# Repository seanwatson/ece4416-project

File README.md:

Engineering 4th Year Design Project:
====================================
Wireless Control System Utilizing Head Movement
===============================================

Description
-----------

As part of the engineering degree program at The University of Western Ontario
all students must complete an eight month design project in their final year
of study. For my project I developed a wireless control system that utilizes
head movement as the input to the system. The goal was to improve accessibility
for patients with limited or no control of their limbs.

For demonstration purposes the device was designed to control the movement and
clicking of a mouse on a computer screen. The device consists of a small,
wearable circuit that is concealed within a baseball cap and software running
on the computer. When the device is within wireless range of the computer it
automatically connects with the computer over bluetooth and
begins translating the user's head motions into mouse movements and clicks on the
screen.

For more information regarding the hardware designs please refer to the "hardware"
directory.

For more information regarding the software please refer to the "software"
directory.

Licenses
--------

The hardware designs in this work are licensed under a Creative Commons Attribution
3.0 license. The software in this work is licensed under the MIT license. Please refer
to the individual hardware and software directories for more information.

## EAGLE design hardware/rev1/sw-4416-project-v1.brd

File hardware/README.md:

Hardware
========

Overview
--------

The hardware consists of a microcontroller, a bluetooth module, an accelerometer, and power management circuitry:

###Microcontroller

- Atmel ATMega32U4
- Programming and debugging over USB port
- UART, ADC
- Deep sleep for power saving

###Bluetooth Module

- Roving Networks RN-42
- Communicates with MCU over UART
- Low power connect, SNIFF mode for power saving

###Accelerometer

- Analog Devices ADP3338
- 3 axis, analog outputs
- Very low power

###Power Management

- 850mA LiPo battery
- 3.3V linear regulator
- LiPo charge controller on board
- Charges over USB

Revisions
---------

The hardware for this project was developed over two revisions:

###Revision 1
- Designed as a development and debugging board for the purpose of easily diagnosing and fixing any bugs.
- Larger parts
- Debugging LEDs
- Debugging jumpers, etc. for the purpose of easily diagnosing and fixing any bugs.

###Revision 2
- Stripped down version of the circuit
- Lower power consumption
- Smaller physical size
- Smaller parts and no debugging features
- Can be concealed within a baseball cap

License
-------

These designs are licensed under a Creative Commons Attribution 3.0 license. See the
LICENSE.txt file for more details.

Acknowledgements
----------------

I'd like to thank the following companies who provided free or discount products and/or services
as part of this school project:

- Alberta Printed Circuits
- Analog Devices
- Atmel
- Microchip
- Roving Networks

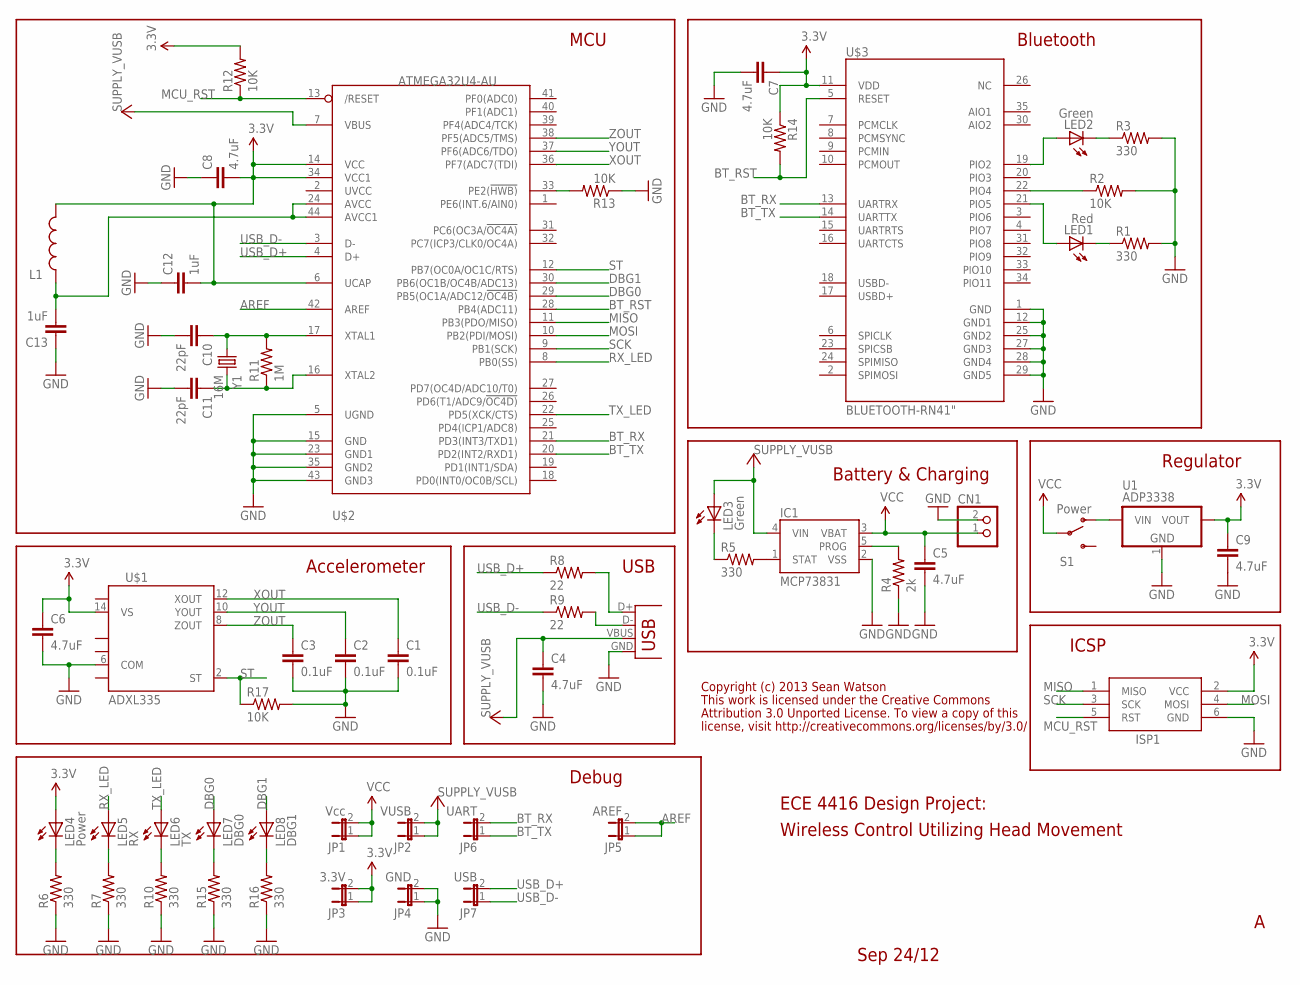
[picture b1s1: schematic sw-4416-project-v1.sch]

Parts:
C1, C2, C3: 0.1uF; 0603-CAP
C4, C5, C6, C7, C8, C9: 4.7uF; 0603-CAP
C10, C11: 22pF; 0603-CAP
C12, C13: 1uF; 0603-CAP
CN1: JST_2PIN-SMT-RA; JST-PH-2-SMT-RA
IC1: MCP73831; SOT23-5
ISP1: AVRISP-6; AVRISP
JP1: Vcc; 1X02
JP2: VUSB; 1X02
JP3: 3.3V; 1X02
JP4: GND; 1X02
JP5: AREF; 1X02
JP6: UART; 1X02
JP7: USB; 1X02
L1: INDUCTOR0805; 0805
LED1: Red; LED-0603
LED2, LED3: Green; LED-0603
LED4: Power; LED-0603
LED5: RX; LED-0603
LED6: TX; LED-0603
LED7: DBG0; LED-0603
LED8: DBG1; LED-0603
R1, R3, R5, R6, R7, R10, R15, R16: 330; 0603-RES
R2, R12, R13, R14, R17: 10K; 0603-RES
R4: 2k; 0603-RES
R8, R9: 22; 0603-RES
R11: 1M; 0603-RES
S1: Power; SWITCH-SPST-SMD-A
U1: ADP3338; SOT-223
U$1: ADXL335; LFCSP-16
U$2: ATMEGA32U4-AU; TQFP44
U$3: BLUETOOTH-RN41"; RN41
X1: USB-MICROB
Y1: 16M; HC49US

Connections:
3.3V: C6.1, C7.1, C8.2, C9.1, C12.2, ISP1.2 (VCC), JP3.1, JP3.2, L1.2, LED4.A, R12.2, R14.1, U1.2 (VOUT), U$1.14 (VS), U$2.6 (UCAP), U$2.14 (VCC), U$2.34 (VCC1), U$3.11 (VDD)
AREF: JP5.1, JP5.2, U$2.42 (AREF)
BT_RST: R14.2, U$2.28 (PB4(ADC11)), U$3.5 (RESET)
BT_RX: JP6.2, U$2.21 (PD3(INT3/TXD1)), U$3.13 (UARTRX)
BT_TX: JP6.1, U$2.20 (PD2(INT2/RXD1)), U$3.14 (UARTTX)
DBG0: LED7.A, U$2.29 (PB5(OC1A/ADC12/!OC4B))
DBG1: LED8.A, U$2.30 (PB6(OC1B/OC4B/ADC13))
GND: C1.2, C2.2, C3.2, C4.2, C5.2, C6.2, C7.2, C8.1, C9.2, C10.2, C11.2, C12.1, C13.1, CN1.2 (1), IC1.2 (VSS), ISP1.6 (GND), JP4.1, JP4.2, R1.2, R2.2, R3.2, R4.1, R6.1, R7.1, R10.1, R13.1, R15.1, R16.1, R17.2, U1.1 (GND), U$1.6 (COM), U$2.5 (UGND), U$2.15 (GND), U$2.23 (GND1), U$2.35 (GND2), U$2.43 (GND3), U$3.1 (GND), U$3.12 (GND1), U$3.25 (GND2), U$3.27 (GND3), U$3.28 (GND4), U$3.29 (GND5), X1.GND
MCU_RST: ISP1.5 (RST), R12.1, U$2.13 (/RESET)
MISO: ISP1.1 (MISO), U$2.11 (PB3(PDO/MISO))
MOSI: ISP1.4 (MOSI), U$2.10 (PB2(PDI/MOSI))
unnamed: LED2.C, R3.1
unnamed: LED1.C, R1.1
unnamed: R2.1, U$3.22 (PIO4)
unnamed: LED2.A, U$3.19 (PIO2)
unnamed: LED1.A, U$3.21 (PIO5)
unnamed: IC1.5 (PROG), R4.2
unnamed: IC1.1 (STAT), R5.2
unnamed: LED3.C, R5.1
unnamed: LED4.C, R6.2
unnamed: LED5.C, R7.2
unnamed: LED6.C, R10.2
unnamed: C10.1, R11.2, U$2.17 (XTAL1), Y1.1
unnamed: C11.1, R11.1, U$2.16 (XTAL2), Y1.2
unnamed: R8.2, X1.D+
unnamed: LED7.C, R15.2
unnamed: C13.2, L1.1, U$2.24 (AVCC), U$2.44 (AVCC1)
unnamed: LED8.C, R16.2
unnamed: R13.2, U$2.33 (PE2(!HWB))
unnamed: R9.2, X1.D-
RX_LED: LED5.A, U$2.8 (PB0(SS))
SCK: ISP1.3 (SCK), U$2.9 (PB1(SCK))
ST: R17.1, U$1.2 (ST), U$2.12 (PB7(OC0A/OC1C/RTS))
TX_LED: LED6.A, U$2.22 (PD5(XCK/CTS))
USB_D+: JP7.2, R8.1, U$2.4 (D+)
USB_D-: JP7.1, R9.1, U$2.3 (D-)
VCC: C5.1, CN1.1 (2), IC1.3 (VBAT), JP1.1, JP1.2, S1.2
VIN: S1.1 (O), U1.3 (VIN)
VUSB: C4.1, IC1.4 (VIN), JP2.1, JP2.2, LED3.A, U$2.7 (VBUS), X1.VBUS
XOUT: C1.1, U$1.12 (XOUT), U$2.36 (PF7(ADC7(TDI))
YOUT: C2.1, U$1.10 (YOUT), U$2.37 (PF6(ADC6/TDO))
ZOUT: C3.1, U$1.8 (ZOUT), U$2.38 (PF5(ADC5/TMS))

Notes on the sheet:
Accelerometer
Bluetooth
MCU
ECE 4416 Design Project:
Wireless Control Utilizing Head Movement
Battery & Charging
USB
Regulator
ICSP
Debug
Sep 24/12
Copyright (c) 2013 Sean Watson
This work is licensed under the Creative Commons
Attribution 3.0 Unported License. To view a copy of this
license, visit http://creativecommons.org/licenses/by/3.0/

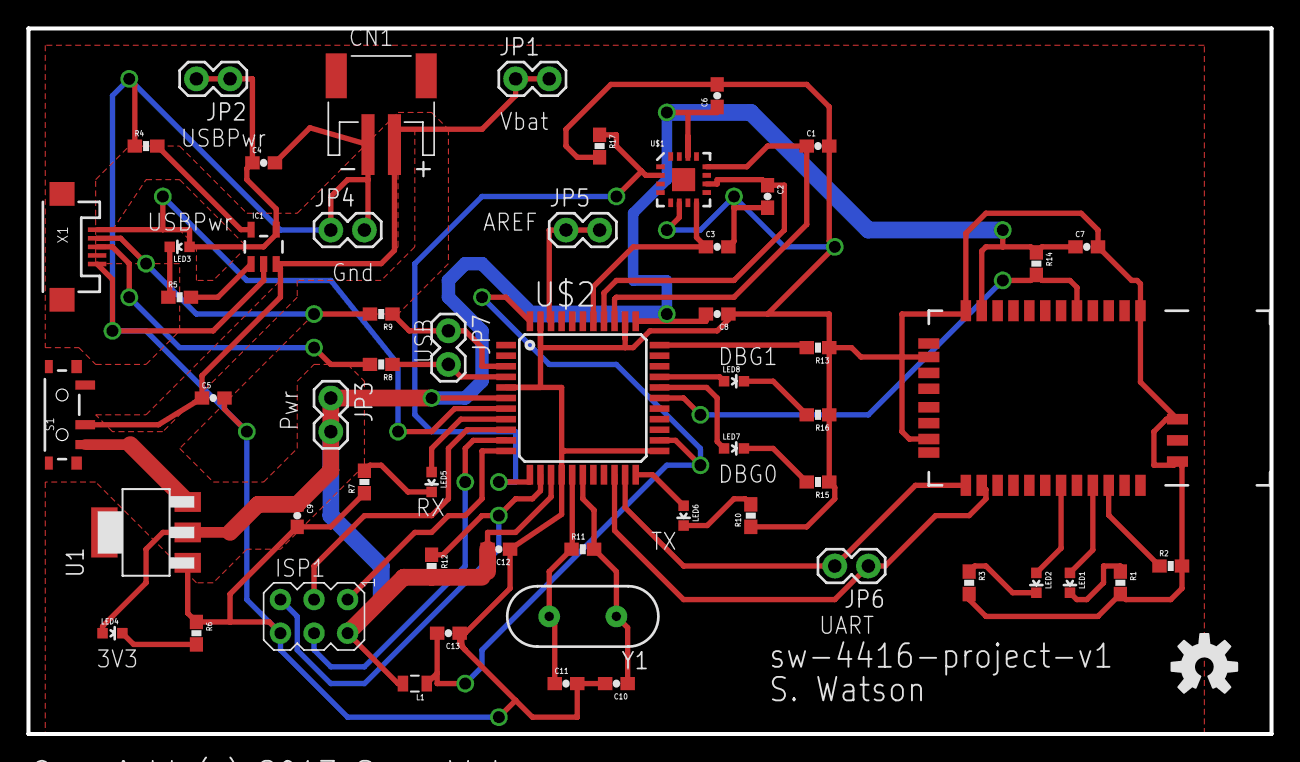
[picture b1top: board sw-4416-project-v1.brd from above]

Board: 2 copper layers, 94.0 x 53.3 mm, 57 parts (0 on the bottom side), 42 nets.

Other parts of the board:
U$4: OSHW-LOGO-M

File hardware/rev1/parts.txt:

Partlist

Exported from sw-4416-project-v1.sch at 12-09-24 6:30 PM

EAGLE Version 6.2.0 Copyright (c) 1988-2012 CadSoft

Assembly variant: 

Part     Value           Device             Package           Library    Sheet

C1       0.1uF           CAP0603-CAP        0603-CAP          SparkFun   1
C2       0.1uF           CAP0603-CAP        0603-CAP          SparkFun   1
C3       0.1uF           CAP0603-CAP        0603-CAP          SparkFun   1
C4       4.7uF           CAP0603-CAP        0603-CAP          SparkFun   1
C5       4.7uF           CAP0603-CAP        0603-CAP          SparkFun   1
C6       4.7uF           CAP0603-CAP        0603-CAP          SparkFun   1
C7       4.7uF           CAP0603-CAP        0603-CAP          SparkFun   1
C8       4.7uF           CAP0603-CAP        0603-CAP          SparkFun   1
C9       4.7uF           CAP0603-CAP        0603-CAP          SparkFun   1
C10      22pF            CAP0603-CAP        0603-CAP          SparkFun   1
C11      22pF            CAP0603-CAP        0603-CAP          SparkFun   1
C12      1uF             CAP0603-CAP        0603-CAP          SparkFun   1
C13      1uF             CAP0603-CAP        0603-CAP          SparkFun   1
CN1                      JST_2PIN-SMT-RA    JST-PH-2-SMT-RA   adafruit   1
IC1      MCP73831        MCP73831           SOT23-5           SparkFun   1
ISP1     AVRISP-6        AVRISP-6           AVRISP            adafruit   1
JP1      Vcc             JUMPER-2PTH        1X02              SparkFun   1
JP2      VUSB            JUMPER-2PTH        1X02              SparkFun   1
JP3      3.3V            JUMPER-2PTH        1X02              SparkFun   1
JP4      GND             JUMPER-2PTH        1X02              SparkFun   1
JP5      AREF            JUMPER-2PTH        1X02              SparkFun   1
JP6      UART            JUMPER-2PTH        1X02              SparkFun   1
JP7      USB             JUMPER-2PTH        1X02              SparkFun   1
JP8      JUMPER-3PTH     JUMPER-3PTH        1X03              SparkFun   1
L1                       INDUCTOR0805       0805              SparkFun   1
LED1     Red             LED0603            LED-0603          SparkFun   1
LED2     Green           LED0603            LED-0603          SparkFun   1
LED3     Green           LED0603            LED-0603          SparkFun   1
LED4     Power           LED0603            LED-0603          SparkFun   1
LED5     RX              LED0603            LED-0603          SparkFun   1
LED6     TX              LED0603            LED-0603          SparkFun   1
LED7     DBG0            LED0603            LED-0603          SparkFun   1
LED8     DBG1            LED0603            LED-0603          SparkFun   1
R1       330             RESISTOR0603-RES   0603-RES          SparkFun   1
R2       10K             RESISTOR0603-RES   0603-RES          SparkFun   1
R3       330             RESISTOR0603-RES   0603-RES          SparkFun   1
R4       2k              RESISTOR0603-RES   0603-RES          SparkFun   1
R5       330             RESISTOR0603-RES   0603-RES          SparkFun   1
R6       330             RESISTOR0603-RES   0603-RES          SparkFun   1
R7       330             RESISTOR0603-RES   0603-RES          SparkFun   1
R8       22              RESISTOR0603-RES   0603-RES          SparkFun   1
R9       22              RESISTOR0603-RES   0603-RES          SparkFun   1
R10      330             RESISTOR0603-RES   0603-RES          SparkFun   1
R11      1M              RESISTOR0603-RES   0603-RES          SparkFun   1
R12      10K             RESISTOR0603-RES   0603-RES          SparkFun   1
R13      10K             RESISTOR0603-RES   0603-RES          SparkFun   1
R14      10K             RESISTOR0603-RES   0603-RES          SparkFun   1
R15      330             RESISTOR0603-RES   0603-RES          SparkFun   1
R16      330             RESISTOR0603-RES   0603-RES          SparkFun   1
R17      10K             RESISTOR0603-RES   0603-RES          SparkFun   1
S1       Power           SWITCH-SPST-SMD-A  SWITCH-SPST-SMD-A SparkFun   1
U$1      ADXL335         ADXL335            LFCSP-16          SparkFun   1
U$2      ATMEGA32U4-AU   ATMEGA32U4-AU      TQFP44            adafruit   1
U$3      BLUETOOTH-RN41" BLUETOOTH-RN41"    RN41              SparkFun   1
U1       ADP3338         VREG_3PINS-SOT-223 SOT-223           dp_devices 1
X1       USB-MICROB      USB-MICROB         USB-MICROB        SparkFun   1
Y1       16M             CRYSTALHC49US      HC49US            SparkFun   1

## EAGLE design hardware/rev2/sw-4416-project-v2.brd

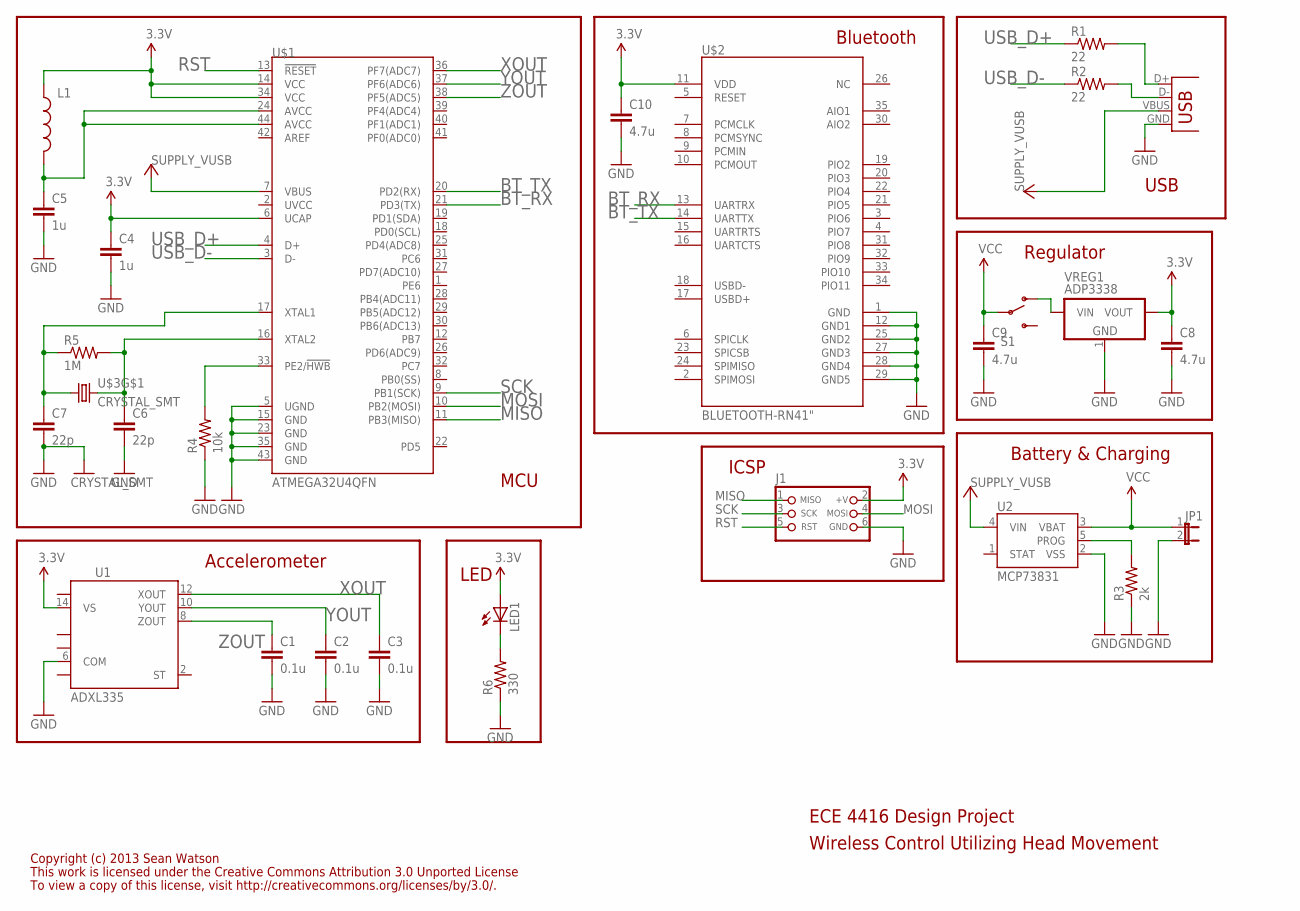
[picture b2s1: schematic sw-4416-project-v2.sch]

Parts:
C1, C2, C3: 0.1u; 0603-CAP
C4, C5: 1u; 0603-CAP
C6, C7: 22p; 0603-CAP
C8, C9, C10: 4.7u; 0603-CAP
J1: CON_HEADER_PRG_AVR_ICSP"; HEADER_PRG_2X03_SMD
JP1: JUMPER-2PTH; 1X02
L1: INDUCTOR0805; 0805
LED1: LED0603; LED-0603
R1, R2: 22; 0603-RES
R3: 2k; 0603-RES
R4: 10k; 0603-RES
R5: 1M; 0603-RES
R6: 330; 0603-RES
S1: SWITCH-SPST-SMD-A
U1: ADXL335; LFCSP-16
U2: MCP73831; SOT23-5
U$1: ATMEGA32U4QFN; QFN-44
U$2: BLUETOOTH-RN41"; RN41
U$3: CRYSTAL_SMT; CRYSTAL-SMD-5X3
VREG1: ADP3338; SOT-223
X1: USB-MICROB

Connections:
3.3V: C4.1, C8.1, C10.1, J1.2 (+V), L1.1, LED1.A, U1.14 (VS), U$1.6 (UCAP), U$1.14 (VCC), U$1.34 (VCC), U$2.11 (VDD), VREG1.2 (VOUT)
BT_RX: U$1.21 (PD3(TX)), U$2.13 (UARTRX)
BT_TX: U$1.20 (PD2(RX)), U$2.14 (UARTTX)
GND: C1.2, C2.2, C3.2, C4.2, C5.2, C6.2, C7.2, C8.2, C9.2, C10.2, J1.6 (GND), JP1.2, R3.1, R4.1, R6.1, U1.6 (COM), U2.2 (VSS), U$1.5 (UGND), U$1.15 (GND), U$1.23 (GND), U$1.35 (GND), U$1.43 (GND), U$2.1 (GND), U$2.12 (GND1), U$2.25 (GND2), U$2.27 (GND3), U$2.28 (GND4), U$2.29 (GND5), U$3.2 (GND), U$3.4 (GND), VREG1.1 (GND), X1.GND
MISO: J1.1 (MISO), U$1.11 (PB3(MISO))
MOSI: J1.4 (MOSI), U$1.10 (PB2(MOSI))
unnamed: S1.1 (O), VREG1.3 (VIN)
unnamed: R2.2, X1.D-
unnamed: R1.2, X1.D+
unnamed: R4.2, U$1.33 (PE2/!HWB)
unnamed: R3.2, U2.5 (PROG)
unnamed: C5.1, L1.2, U$1.24 (AVCC), U$1.44 (AVCC)
unnamed: C6.1, R5.2, U$1.16 (XTAL2), U$3.3 (2)
unnamed: C7.1, R5.1, U$1.17 (XTAL1), U$3.1
unnamed: LED1.C, R6.2
RST: J1.5 (RST), U$1.13 (!RESET)
SCK: J1.3 (SCK), U$1.9 (PB1(SCK))
USB_D+: R1.1, U$1.4 (D+)
USB_D-: R2.1, U$1.3 (D-)
VCC: C9.1, JP1.1, S1.2, U2.3 (VBAT)
VUSB: U2.4 (VIN), U$1.7 (VBUS), X1.VBUS
XOUT: C3.1, U1.12 (XOUT), U$1.36 (PF7(ADC7))
YOUT: C2.1, U1.10 (YOUT), U$1.37 (PF6(ADC6))
ZOUT: C1.1, U1.8 (ZOUT), U$1.38 (PF5(ADC5))

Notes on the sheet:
Regulator
USB
Battery & Charging
Bluetooth
ECE 4416 Design Project
Wireless Control Utilizing Head Movement
Accelerometer
MCU
ICSP
LED
Copyright (c) 2013 Sean Watson
This work is licensed under the Creative Commons Attribution 3.0 Unported License
To view a copy of this license, visit http://creativecommons.org/licenses/by/3.0/.

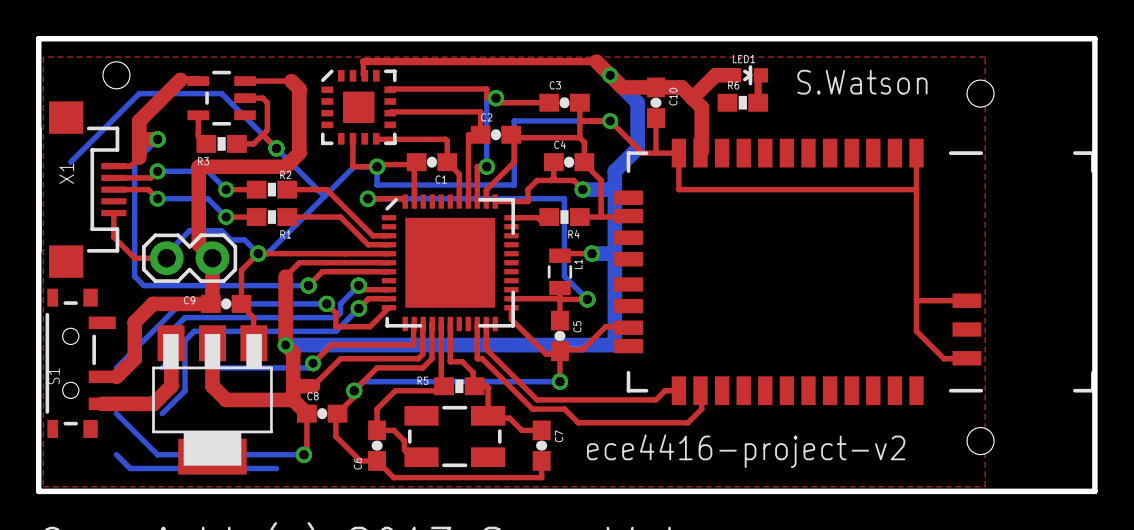
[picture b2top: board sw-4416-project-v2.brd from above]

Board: 2 copper layers, 58.7 x 25.1 mm, 28 parts (1 on the bottom side), 24 nets.

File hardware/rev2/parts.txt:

Partlist

Exported from sw-4416-project-v2.sch at 13-01-15 9:42 AM

EAGLE Version 6.2.0 Copyright (c) 1988-2012 CadSoft

Assembly variant: 

Part     Value                    Device                   Package             Library    Sheet

C1       0.1u                     CAP0603-CAP              0603-CAP            SparkFun   1
C2       0.1u                     CAP0603-CAP              0603-CAP            SparkFun   1
C3       0.1u                     CAP0603-CAP              0603-CAP            SparkFun   1
C4       1u                       CAP0603-CAP              0603-CAP            SparkFun   1
C5       1u                       CAP0603-CAP              0603-CAP            SparkFun   1
C6       22p                      CAP0603-CAP              0603-CAP            SparkFun   1
C7       22p                      CAP0603-CAP              0603-CAP            SparkFun   1
C8       4.7u                     CAP0603-CAP              0603-CAP            SparkFun   1
C9       4.7u                     CAP0603-CAP              0603-CAP            SparkFun   1
C10      4.7u                     CAP0603-CAP              0603-CAP            SparkFun   1
J1       CON_HEADER_PRG_AVR_ICSP" CON_HEADER_PRG_AVR_ICSP" HEADER_PRG_2X03_SMD dp_devices 1
JP1                               JUMPER-2PTH              1X02                SparkFun   1
L1                                INDUCTOR0805             0805                SparkFun   1
LED1                              LED0603                  LED-0603            SparkFun   1
R1       22                       RESISTOR0603-RES         0603-RES            SparkFun   1
R2       22                       RESISTOR0603-RES         0603-RES            SparkFun   1
R3       2k                       RESISTOR0603-RES         0603-RES            SparkFun   1
R4       10k                      RESISTOR0603-RES         0603-RES            SparkFun   1
R5       1M                       RESISTOR0603-RES         0603-RES            SparkFun   1
R6       330                      RESISTOR0603-RES         0603-RES            SparkFun   1
S1                                SWITCH-SPST-SMD-A        SWITCH-SPST-SMD-A   SparkFun   1
U$1      ATMEGA32U4QFN            ATMEGA32U4QFN            QFN-44              SparkFun   1
U$2      BLUETOOTH-RN41"          BLUETOOTH-RN41"          RN41                SparkFun   1
U$3      CRYSTAL_SMT              CRYSTAL_SMT              CRYSTAL-SMD-5X3     SparkFun   1
U1       ADXL335                  ADXL335                  LFCSP-16            SparkFun   1
U2       MCP73831                 MCP73831                 SOT23-5             SparkFun   1
VREG1    ADP3338                  VREG_3PINS-SOT-223       SOT-223             dp_devices 1
X1       USB-MICROB               USB-MICROB               USB-MICROB          SparkFun   1

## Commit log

2012-09-23 Adding partially completed schematic
2012-09-23 Added power circuitry
2012-09-24 changing repo structure
2012-09-24 removing old schematic
2012-09-24 schematic version 1 completed
2012-10-02 rev 1 board finished
2012-12-24 Adding BluetoothConnection class for client
2012-12-24 moving mouse from commands in a queue
2012-12-26 can detect composite motions
2012-12-27 some documenting
2013-01-02 testing accelerometer
2013-01-02 testing sketch
2013-01-12 rev 2 board
2013-01-12 working on embedded side code
2013-01-12 cleaning up
2013-01-12 more cleaning
2013-01-12 rev2 design done
2013-01-15 second rev completed
2013-02-05 working demo code
2013-02-06 Auto MAC detection, logging, some cleaning
2013-02-23 made a calibration utility, added slow/fast motions
2013-02-24 two way communication, automatic connection retries, and sleep mode added
2013-02-25 Automatic reconnect feature added
2013-02-25 Cleaning and documentation
2013-02-26 open sourcing hardware and software
2013-02-27 Adding readmes
2013-02-27 fixing markdown issue
2013-03-13 calibrated with device in case
2013-03-20 wireless calibration without having to reboot done

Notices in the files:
parts and their libraries:
SparkFun: Licensing: CC v3.0 Share-Alike You are welcome to use this library for commercial purposes.
